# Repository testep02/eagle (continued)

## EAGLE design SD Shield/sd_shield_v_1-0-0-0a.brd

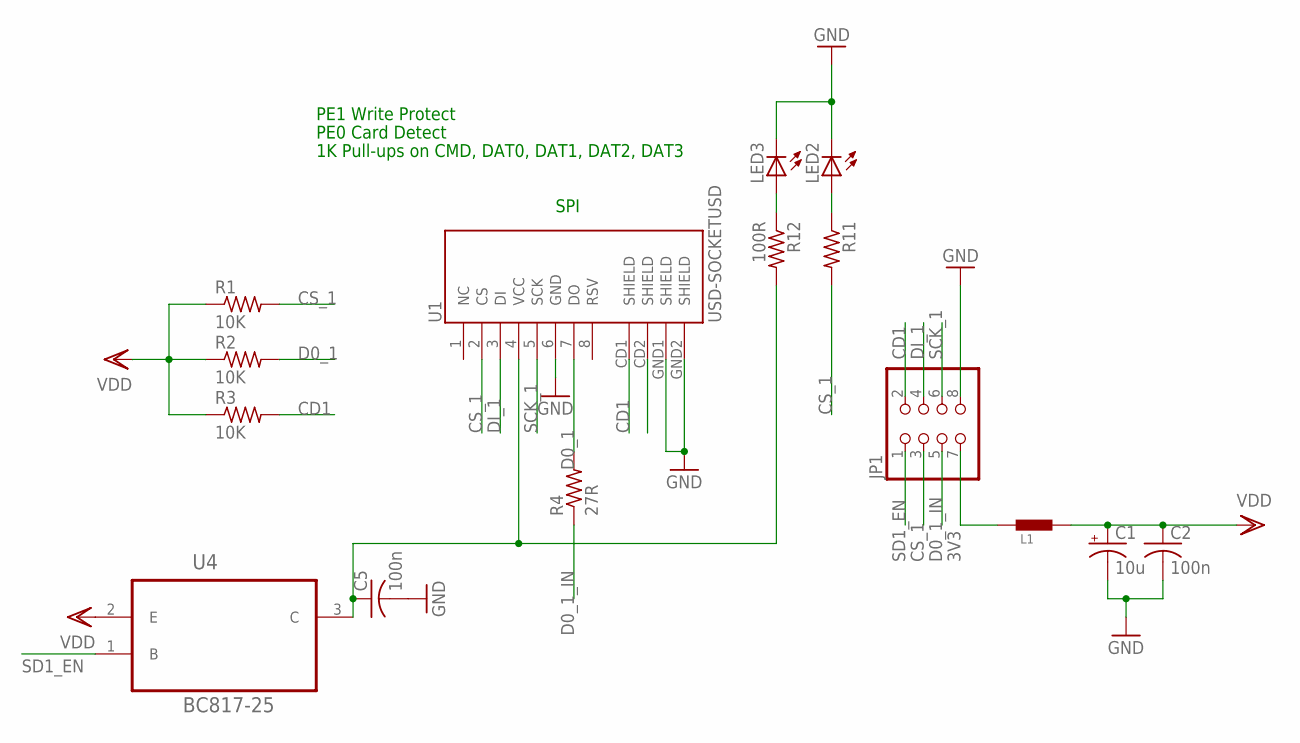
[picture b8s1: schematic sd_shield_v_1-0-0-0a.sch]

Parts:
C1: 10u; B/3528-21W
C2, C5: 100n; C0603
JP1: PINHD-2X4; 2X04
L1: FERRITE; 0805
LED2, LED3: LEDCHIP-LED0603; CHIP-LED0603
R1, R2, R3: 10K; R0603
R4: 27R; R0603
R11: R-US_R0603; R0603
R12: 100R; R0603
U1: USD-SOCKETUSD; USD-SOCKET-PP
U4: BC817-25; SOT95P240X97-3N

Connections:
3V3: JP1.7, L1.1
CD1: JP1.2, R3.2, U1.CD1 (SHIELD)
CS_1: JP1.3, R1.2, R11.2, U1.2 (CS)
D0_1: R2.2, R4.2, U1.7 (DO)
D0_1_IN: JP1.5, R4.1
DI_1: JP1.4, U1.3 (DI)
GND: C1.-, C2.2, C5.2, JP1.8, LED2.C, LED3.C, U1.6 (GND), U1.GND1 (SHIELD), U1.GND2 (SHIELD)
unnamed: LED2.A, R11.1
unnamed: LED3.A, R12.1
unnamed: C5.1, R12.2, U1.4 (VCC), U4.3 (C)
SCK_1: JP1.6, U1.5 (SCK)
SD1_EN: JP1.1, U4.1 (B)
VDD: C1.+, C2.1, L1.2, R1.1, R2.1, R3.1, U4.2 (E)

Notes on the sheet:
SPI
1K Pull-ups on CMD, DAT0, DAT1, DAT2, DAT3
PE0 Card Detect
PE1 Write Protect

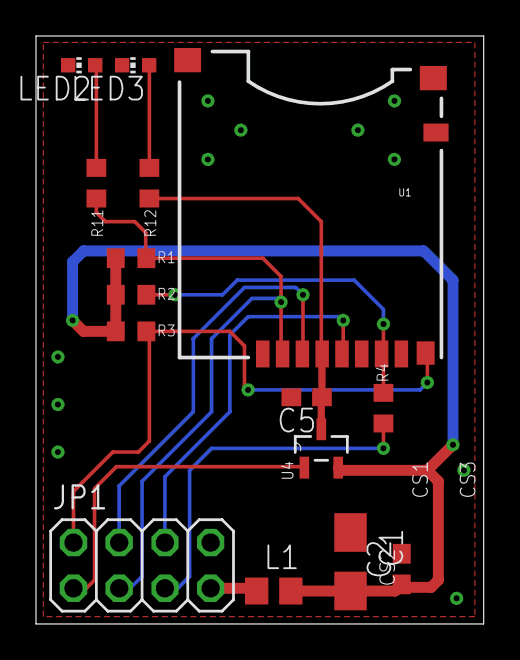
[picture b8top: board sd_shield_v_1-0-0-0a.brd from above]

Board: 2 copper layers, 24.9 x 32.7 mm, 15 parts (0 on the bottom side), 13 nets.
